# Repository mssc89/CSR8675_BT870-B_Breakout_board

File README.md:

# CSR8675/BT870-B Breakout board

EAGLE files for CSR8675 aka BT870-B dev module breakout board.

It allows easy programmer, audio input and power connections. Includes mandatory power input resistor and BT antenna. Created for use with 5th gen iPod (hence the small footprint).

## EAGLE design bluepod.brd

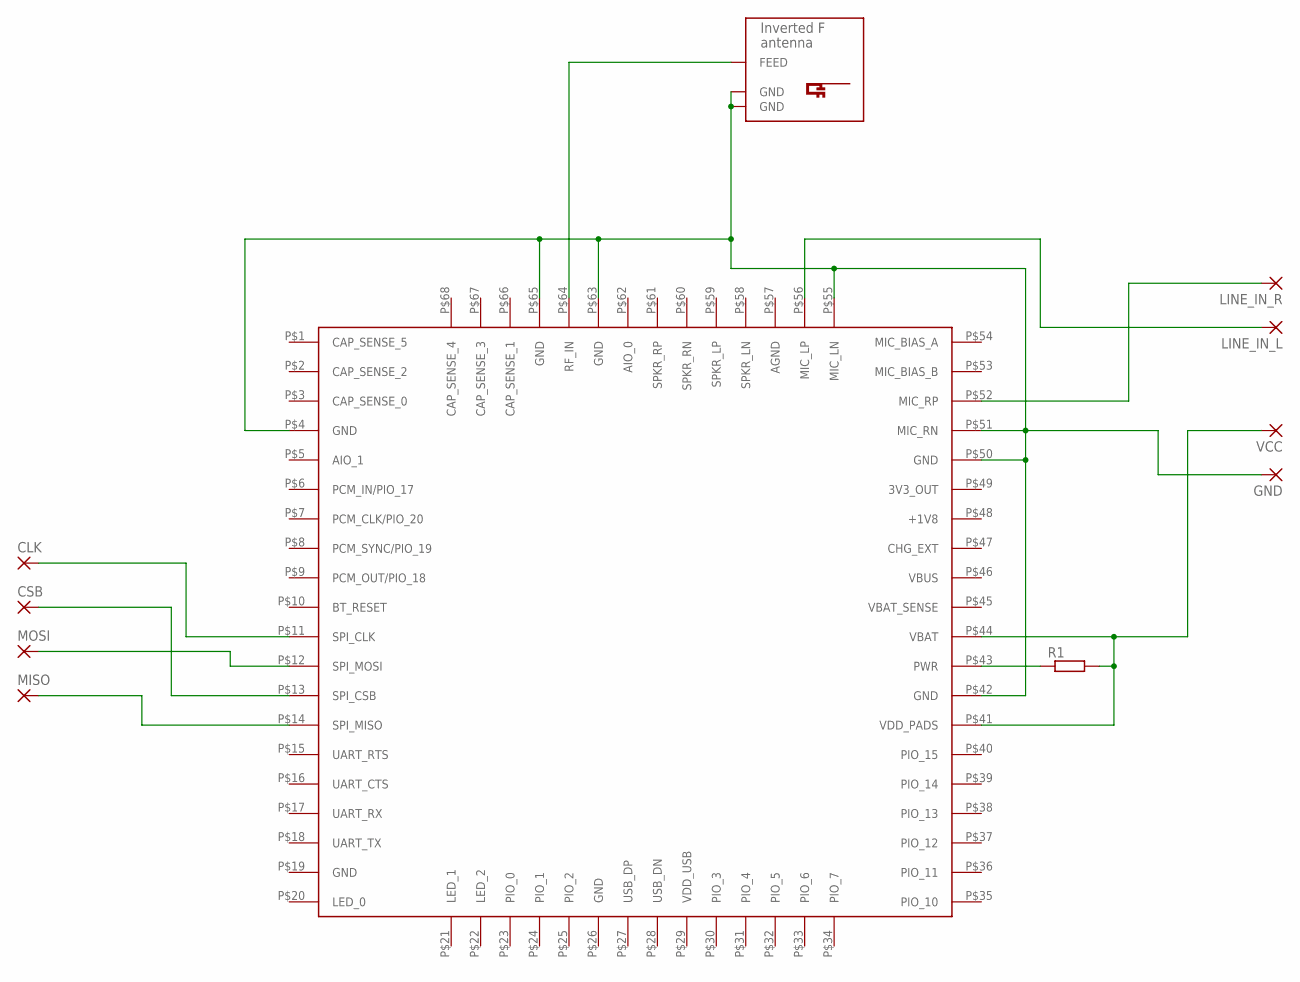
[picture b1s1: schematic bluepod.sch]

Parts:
CLK: 2,54/1,0
CSB: 2,54/1,0
GND: 2,54/1,0
LINE_IN_L: 2,54/1,0
LINE_IN_R: 2,54/1,0
MISO: 2,54/1,0
MOSI: 2,54/1,0
R1: R-EU_0207/5V; 0207/5V
U$1: BTM875-B; STANDARD
U$2: INVERTED_F_ANTENNA+0; DN007+0
VCC: 2,54/1,0

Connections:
unnamed: CLK.1, U$1.P$11 (SPI_CLK)
unnamed: CSB.1, U$1.P$13 (SPI_CSB)
unnamed: MOSI.1, U$1.P$12 (SPI_MOSI)
unnamed: MISO.1, U$1.P$14 (SPI_MISO)
unnamed: LINE_IN_R.1, U$1.P$52 (MIC_RP)
unnamed: LINE_IN_L.1, U$1.P$56 (MIC_LP)
unnamed: GND.1, U$1.P$4 (GND), U$1.P$42 (GND), U$1.P$50 (GND), U$1.P$51 (MIC_RN), U$1.P$55 (MIC_LN), U$1.P$63 (GND), U$1.P$65 (GND), U$2.GND, U$2.GND@1 (GND)
unnamed: U$1.P$64 (RF_IN), U$2.FEED
unnamed: R1.1, U$1.P$43 (PWR)
unnamed: R1.2, U$1.P$41 (VDD_PADS), U$1.P$44 (VBAT), VCC.1

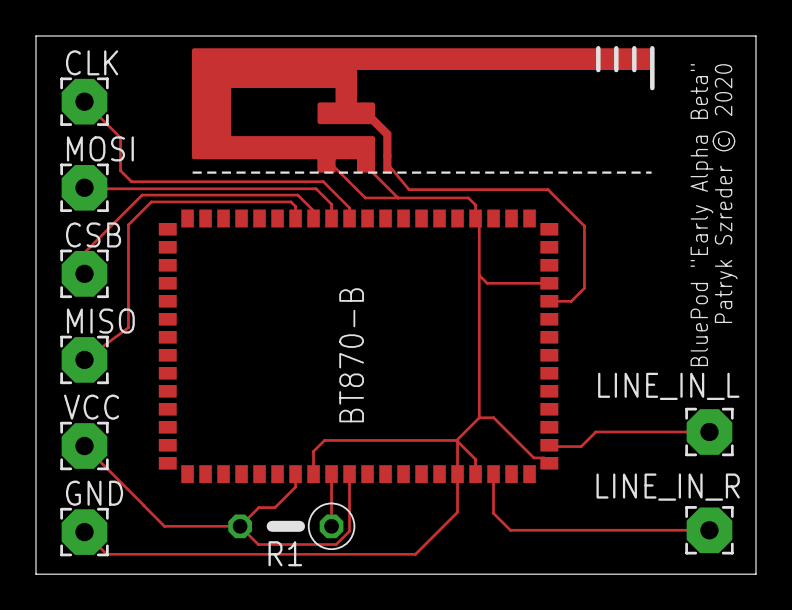
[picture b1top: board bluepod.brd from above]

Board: 2 copper layers, 40.0 x 29.9 mm, 11 parts (0 on the bottom side), 10 nets.

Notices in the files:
bluepod.brd:
Patryk Szreder © 2020
